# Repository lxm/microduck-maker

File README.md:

# MicroDuck Maker

**把 MicroDuck 从装配、标定到日常维护会用到的工具，放进一个持续维护的项目。**

[工具目录](tools/README.md) · [飞特舵机调试](tools/servo-debug/README.md) · [标定工具使用说明](tools/calibrator/README.md) · [装配对照](tools/servo-guide/README.md) · [下载发布包](https://github.com/lxm/microduck-maker/releases) · [反馈问题](https://github.com/lxm/microduck-maker/issues)

## 现在可以用什么

| 工具 | 用途 | 入口 |
|---|---|---|
| 飞特舵机调试 | USB 串口直连 HD-1910：搜索、微调、反馈曲线、校零与参数备份 | [tools/servo-debug](tools/servo-debug/) |
| 逐关节零位标定 | 单屏 3D 工作台、逐颗标定、回零 / HOME、保持与备份 | [tools/calibrator](tools/calibrator/) |
| 舵机编号与装配对照 | 飞特 HD-1910 版的 15 颗舵机位置、编号与装配检查 | [tools/servo-guide](tools/servo-guide/) · [在线查看](https://lxm.github.io/microduck-servo-guide/) |
| 零位标定支架 | 6 件 STL、装配参考与代打说明 | [tools/zero-fixture](tools/zero-fixture/) |
| 硅胶脚底翻模（正在尝试中） | 原尺寸版固定失败、需皮筋兜住；本次硅胶很防滑，后续 A–D 四版待实验 | [下载模具与使用方法](tools/silicone-sole-mold/) |
| 颈部舵机连接板 | D0.8.1 原配胶壳短线焊接版：KiCad、板级 3D、单板／六联制造文件与接线说明 | [tools/neck-interconnect](tools/neck-interconnect/) |

仓库包含标定与装配工具的源码、第三方资源、使用说明和离线验证程序，以及零位标定支架的 STL 打印文件（不含支架 STEP）、颈部连接板的可编辑 PCB 和板级 STEP。支架保留原设计，已知配合问题和来源说明见其目录。颈部板当前收录原配胶壳短线穿孔焊接版，替代端子试装版待验证后单独发布。

## Orange Pi Zero 3W 固件

基于 [kissqy/Microduck-kissqy（`d4d21c1`）](https://github.com/kissqy/Microduck-kissqy/tree/d4d21c1073d2c12ad2b5dfe3deb031030f7792ef)，保留原有机器人应用、模型和 ToF 源码，由 MicroDuck Maker 在 Armbian 26.8.1 上适配串口、HAT I²C 和音频。

摄像头版镜像请从 [Orange Pi 固件 Actions](https://github.com/lxm/microduck-maker/actions/workflows/orangepi-image.yml) 的成功构建下载。下方固定发布版 exp.1 早于摄像头适配。

[下载 exp.1 完整刷卡镜像（.img.xz）](https://github.com/lxm/microduck-maker/releases/download/orangepi-zero3w-exp.1/Microduck_OrangePiZero3W_Experimental.img.xz) · [SHA-256 校验文件](https://github.com/lxm/microduck-maker/releases/download/orangepi-zero3w-exp.1/SHA256SUMS) · [刷卡与首次启动说明](firmware/orangepi-zero3w/)

这是面向 Allwinner A733、1 GB、PCB V1.5 的实验镜像，已离线校验，尚未验证本发布镜像的实机启动。

## 先体验标定工具

电脑安装 Python **3.10+**，然后运行：

```sh
git clone https://github.com/lxm/microduck-maker.git
cd microduck-maker/tools/calibrator
python3 server.py --demo
```

打开 <http://127.0.0.1:8795/>。默认即为模拟模式，可以体验选关节、采样、保存和保持流程，不连接机器人。下载资源均包含在仓库中，不需要 npm 或在线 CDN。

需要另一台电脑访问时，在启动命令后加 `--bind 0.0.0.0`，然后用浏览器打开 `http://服务电脑的IPv4地址:8795/`。具体步骤与连接排查见 [局域网访问说明](tools/calibrator/docs/usage.md#从另一台电脑访问)。

实机标定还需要兼容的板端运行环境与 SSH。先读 [适用范围与连接方法](tools/calibrator/README.md#适用范围)，再按 [详细操作说明](tools/calibrator/docs/usage.md) 执行。机械零位和站立 HOME 是不同概念，3D 参考按钮只改变画面。

## 直接连接飞特舵机

电脑通过 USB 转 TTL 转接器连接 HD-1910 时，使用 [MicroDuck FD 调试工作台](tools/servo-debug/README.md)。macOS 可双击 `tools/servo-debug/启动调试工具.command`，或从仓库根目录执行：

```sh
zsh tools/servo-debug/启动调试工具.command
```

选择「演示设备」可先体验完整流程；实机使用前按工具说明核对供电、串口与波特率。它与通过 SSH 操作机器人主板的标定工具是两个独立入口。

## 项目结构

```text
microduck-maker/
├── tools/
│   ├── servo-debug/      # USB 串口舵机调试工作台与演示设备
│   ├── calibrator/       # 标定网页、板端代理、测试与说明
│   ├── servo-guide/      # 3D 舵机编号与装配对照
│   ├── zero-fixture/     # 零位标定支架 STL 与打印说明
│   ├── silicone-sole-mold/ # 硅胶脚套模具与浇注说明（正在尝试中）
│   └── neck-interconnect/ # 颈部连接板、板级模型与接线／打板说明
├── firmware/             # 按板型维护的固件源码与镜像构建说明
├── docs/                 # 项目维护与发布说明
├── scripts/              # 全仓库离线验证
├── .github/workflows/    # 自动校验
├── LICENSE              # 原创代码的 MIT 许可
└── THIRD_PARTY_NOTICES.md
```

每个工具在自己的目录内说明依赖、启动方式、兼容范围和来源，能够独立使用。后续新增工具继续放到 `tools/<工具名>/`，固件按板型放到 `firmware/<板型>/`。

## 开发与验证

安装 Python 3.10+ 和 Node.js。Node.js 仅用于 JavaScript 语法校验，不是标定工具的运行依赖。

```sh
python3 -m pip install -r tools/servo-debug/requirements.txt
python3 scripts/validate.py
```

验证包含飞特调试工具的模拟协议、校零与 HTTP 检查，以及标定工具及串口发现/依赖准备的离线测试、3D 引用文件哈希、网页静态资源，以及装配对照的网格、69 个装配变换和 15 个舵机编号、颈部板文件与制造包完整性。验证不连接机器人、不操作串口、不上传程序或改写实机。

当前工作台增加单屏布局与回 HOME 操作；离线测试通过不等同于跨机型实机验收。兼容条件及已知边界见各工具说明。贡献与发布方式见 [CONTRIBUTING.md](CONTRIBUTING.md) 和 [发布说明](docs/releasing.md)。

## 来源与许可

- 飞特舵机调试工作台继承原项目原创工具的 Apache-2.0 许可，来源和修改范围见 [工具说明](tools/servo-debug/README.md#目录与来源)。
- lxm 原创的标定界面、维护代理、脚本，以及装配对照的原创网页和提取代码采用 [MIT](LICENSE)。
- 标定工具引用的 Kissqy 参考代码保留其**个人非商业使用许可**；其 3D 模型与 Three.js 分别保留上游模型许可、MIT 许可。
- 装配工具的 CAD 衍生模型采用 **CC BY-NC-SA 4.0**，保留机械行者Robo、fanhao375 和 Pollen Robotics 的署名。
- 零位标定支架来自交流群分享，暂无原始发布链接，作者与模型许可尚未确认；其 STL 与模型截图不纳入软件 MIT 许可，详见该目录说明。
- 颈部板的原创 PCB、简化接线模型、脚本与说明适用 MIT；原配胶壳模型为示意，原厂舵机 CAD 未打包，见 [资料来源](tools/neck-interconnect/d0.8.1/docs/provenance.md)。
- 不同目录的许可范围见 [THIRD_PARTY_NOTICES.md](THIRD_PARTY_NOTICES.md)。MIT 不覆盖上述单独授权的资源，不能将整个下载包理解为统一 MIT 授权。

这是独立社区项目，与 Pollen Robotics、飞特及所引用社区项目无官方隶属或背书关系。现有 [microduck-servo-guide](https://github.com/lxm/microduck-servo-guide) 仓库和在线页面继续保留，新项目统一收录后续工具源码。

English: A growing collection of MicroDuck maker tools for assembly, servo zero calibration and maintenance. The calibration UI runs locally with an offline demo; hardware mode requires a compatible HD1910 robot environment. Third-party code and model assets retain their own licenses.

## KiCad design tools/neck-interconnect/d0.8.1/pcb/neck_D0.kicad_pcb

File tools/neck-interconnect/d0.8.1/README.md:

# D0.8.1 原配胶壳短线穿孔焊接版

整理日期：2026-11-02。设计快照：2026-11-01。

本版保留原配 AMP2.0 胶壳、压接触点和短线，裸线端穿过 J1–J4 的原通孔，在 PCB 外侧焊接。板厚 1.6mm，主体宽 20mm、包围尺寸 25.5×40mm，四个固定孔，外接凸台在正面左侧。PCB 直接贴舵机参考安装面，没有垫高结构；接头和线长以实物试装确定。

相比旧 D0.8，已修正 J1/J2 的 DATA/GND 铜网与编号，补齐六个端口及三个测试点的双面丝印，测试点加大为 Ø1.8mm 焊盘／Ø0.5mm 孔。旧错误包未收录。这里没有替代排母焊盘、大搭焊接线焊盘或 7343 电容封装。

## 下载与打开

- [KiCad 工程](pcb/neck_D0.kicad_pro)、[PCB](pcb/neck_D0.kicad_pcb)、[原理图](pcb/neck_D0.kicad_sch)。整目录下载后，用 KiCad 10 打开工程；本地符号库、封装库与模型按相对路径组织。
- [不含舵机的 PCB 查看副本](pcb/neck_D0_8_1_no_servos.kicad_pcb)、[完全裸板查看副本](pcb/neck_D0_8_1_bare_pcb_view.kicad_pcb)。主工程同样只收录板级模型。PCB 编辑器中用“视图 → 3D 查看器”查看，切换正反面。
- [板级 STEP](mechanical/KiCad_Neck_D0_8_1_PCB_only.step)，可用 FreeCAD 等查看。包含 PCB、铜与简化连接器／线端模型，不含原厂舵机 CAD。
- [单板 Gerber ZIP](fabrication/D0_8_1_1oz_single/MicroDuck_Neck_D0.8.1_1oz_single_25.5x40_PINOUT_CHECK.zip)、[六联 Gerber ZIP](fabrication/D0_8_1_1oz_6up/MicroDuck_Neck_D0.8.1_1oz_6up_94.5x96_PINOUT_CHECK.zip)。在 GitHub 文件页点击下载原始文件，再将 ZIP 上传打板平台。
- [物料表](bom.csv)、[接线装配](docs/assembly.md)、[针序表](docs/pinout-and-testpoints.md)、[打板参数](docs/fabrication.md)。

## 正反面

下图为裸板，不显示连接器。F 面朝外，B 面朝舵机。正面凸台在左，翻到背面后自然显示在右侧。

## 供电与验收状态

六个端口并联：1=DATA，2=VBUS_SERVO，3=GND。**+ 为电池母线，2S 最高 8.4V；本板没有降压电路。** 头部若使用 Zero 3W 等主板，应由对应供电电路降压后接入，不能把该 + 直接当作 5V。

本版内部 ERC、DRC、针序、丝印、测试点、六联一致性及 Gerber 导出检查通过。整理后再次运行主工程 ERC、DRC 和原理图一致性检查；[当前打包 DRC](validation/packaged-drc.json)、[ERC](validation/packaged-erc.json)、[文件清单](manifest.json)及[原检查记录](validation/original/)一并保留。

J1/J2 的修正来自先前实物错误反馈；**J5/J6 外接线束另一端极性仍待实物核对**。短线穿孔、螺钉规格和有效深度、完整运动范围、接线抗拉及实际负载温升也尚未完成样板验收。检查通过表示文件内部一致，不表示整机配合已经验证。使用前按装配说明逐项核对。

PCB、原创脚本和说明适用仓库 MIT 许可。连接器模型按尺寸简化，原配胶壳／线端仅作装配示意，不是供应商精确 CAD 或替代接头认证。来源与整理改动见 [provenance.md](docs/provenance.md)。

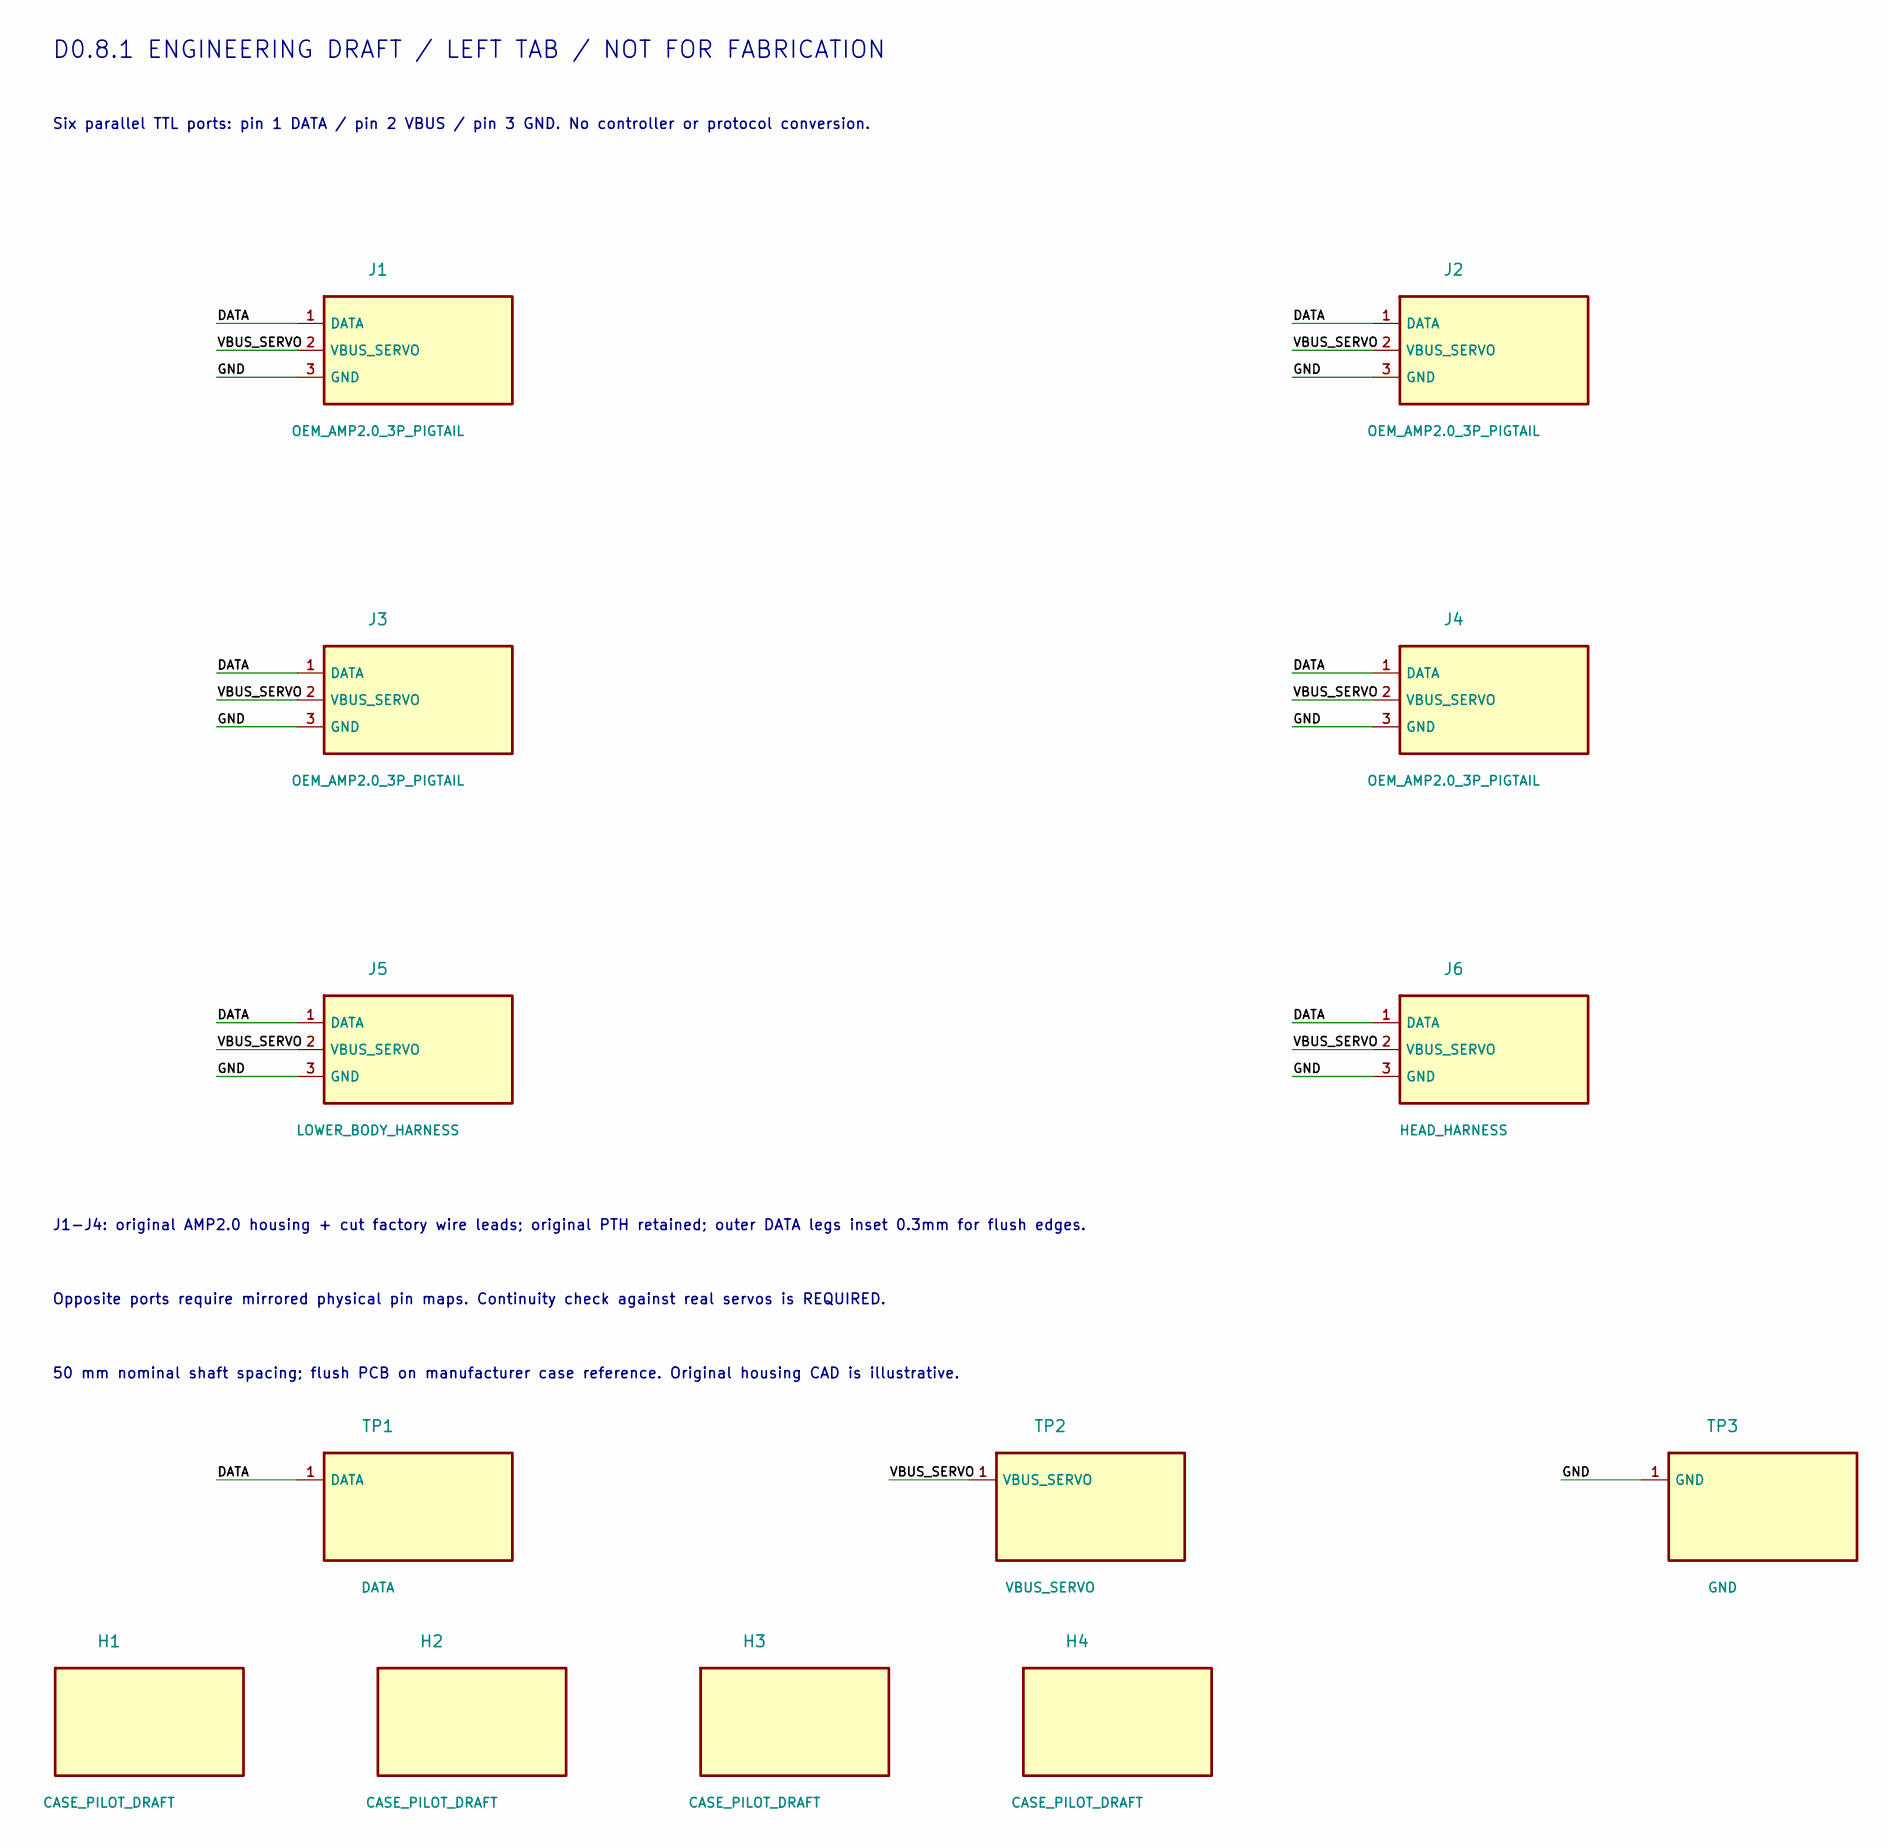
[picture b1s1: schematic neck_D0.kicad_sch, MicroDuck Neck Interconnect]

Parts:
H1: CASE_PILOT_DRAFT; CaseMount_Lower_AssemblyReference
H2, H4: CASE_PILOT_DRAFT; CaseMount_D2
H3: CASE_PILOT_DRAFT; CaseMount_Upper_AssemblyReference
J1, J3: OEM_AMP2.0_3P_PIGTAIL; OEM_WirePTH_P2mm_Pin1Left; MPN NOT_IDENTIFIED_OEM_SUPPLIED
J2, J4: OEM_AMP2.0_3P_PIGTAIL; OEM_WirePTH_P2mm_Pin1Right; MPN NOT_IDENTIFIED_OEM_SUPPLIED
J5: LOWER_BODY_HARNESS; CJT_A2007WV_3P; MPN A2007WV-3P
J6: HEAD_HARNESS; CJT_A2007WV_3P; MPN A2007WV-3P
TP1: DATA; TP_PTH_1p8
TP2: VBUS_SERVO; TP_PTH_1p8
TP3: GND; TP_PTH_1p8

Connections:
/DATA: J1.1 (DATA), J2.1 (DATA), J3.1 (DATA), J4.1 (DATA), J5.1 (DATA), J6.1 (DATA), TP1.1
/GND: J1.3 (GND), J2.3 (GND), J3.3 (GND), J4.3 (GND), J5.3 (GND), J6.3 (GND), TP3.1
/VBUS_SERVO: J1.2 (VBUS_SERVO), J2.2 (VBUS_SERVO), J3.2 (VBUS_SERVO), J4.2 (VBUS_SERVO), J5.2 (VBUS_SERVO), J6.2 (VBUS_SERVO), TP2.1

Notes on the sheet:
D0.8.1 ENGINEERING DRAFT / LEFT TAB / NOT FOR FABRICATION
Six parallel TTL ports: pin 1 DATA / pin 2 VBUS / pin 3 GND. No controller or protocol conversion.
J1-J4: original AMP2.0 housing + cut factory wire leads; original PTH retained; outer DATA legs inset 0.3mm for flush edges.
Opposite ports require mirrored physical pin maps. Continuity check against real servos is REQUIRED.
50 mm nominal shaft spacing; flush PCB on manufacturer case reference. Original housing CAD is illustrative.

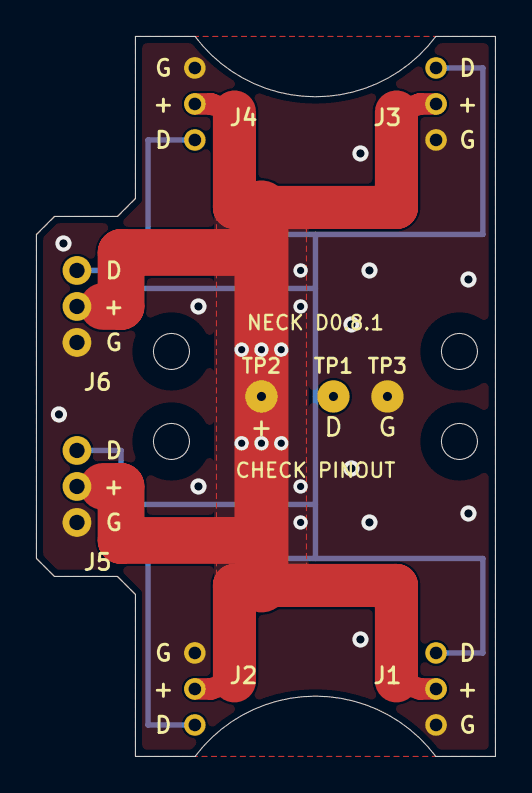
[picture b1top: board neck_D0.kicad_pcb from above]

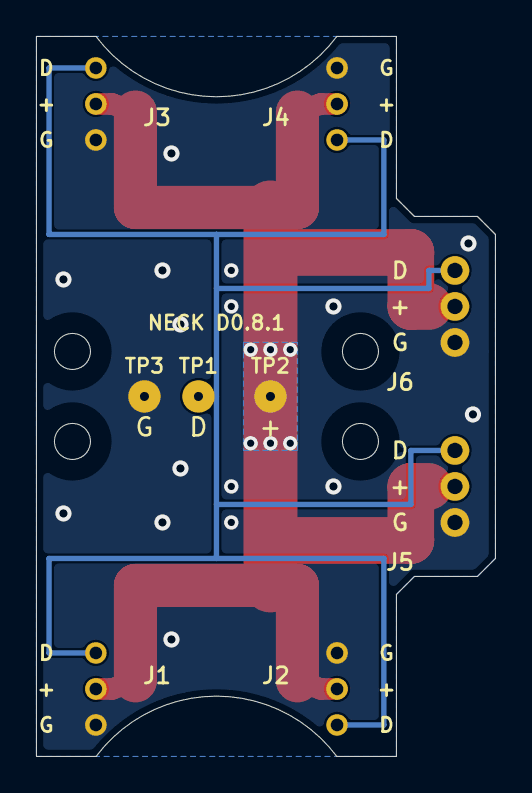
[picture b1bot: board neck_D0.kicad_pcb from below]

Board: 2 copper layers, 25.5 x 40.0 mm, 13 parts (6 on the bottom side), 3 nets.

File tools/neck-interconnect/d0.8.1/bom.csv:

Reference,Qty,Value,Footprint,MPN,Manufacturer,Chosen_Distributor,Datasheet,Validated,DNP,Notes
"J1,J3",2,OEM_AMP2.0_3P_PIGTAIL,OEM_WirePTH_P2mm_Pin1Left,NOT_IDENTIFIED_OEM_SUPPLIED,FEETECH supplied harness,,,,,Reuse one original servo-supplied AMP2.0 plug with 3 factory wires per port. Trim/strip ends to original 0.70mm PTH; solder only outside. Original wire OD and plug seating need dry fit.
"J2,J4",2,OEM_AMP2.0_3P_PIGTAIL,OEM_WirePTH_P2mm_Pin1Right,NOT_IDENTIFIED_OEM_SUPPLIED,FEETECH supplied harness,,,,,Reuse one original servo-supplied AMP2.0 plug with 3 factory wires per port. Trim/strip ends to original 0.70mm PTH; solder only outside. Original wire OD and plug seating need dry fit.
J5,1,LOWER_BODY_HARNESS,CJT_A2007WV_3P,A2007WV-3P,CJT,,https://www.cjt.com/upload/A2007.pdf,,,External harness socket; mating compatibility and wire orientation require sample check.
J6,1,HEAD_HARNESS,CJT_A2007WV_3P,A2007WV-3P,CJT,,https://www.cjt.com/upload/A2007.pdf,,,External harness socket; mating compatibility and wire orientation require sample check.

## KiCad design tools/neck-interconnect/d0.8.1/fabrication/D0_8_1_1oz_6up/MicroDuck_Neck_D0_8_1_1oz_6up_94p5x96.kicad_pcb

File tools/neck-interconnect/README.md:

# 颈部舵机连接板

将两只颈部舵机的 DATA、电池电源与地汇接到一块 PCB，通过左侧两个插座连接下半身和头部，减少颈部独立线束。PCB 主体与舵机参考外壳齐边，直接贴壳安装，不设垫柱。

当前收录 **[D0.8.1 原配胶壳短线穿孔焊接版](d0.8.1/README.md)**。它使用舵机原配 AMP2.0 胶壳、原压接触点和剪短的原配线，线端穿 PCB 通孔，在外侧焊接。J5/J6 使用 A2007WV-3P。它是带检查记录的原型资料，不是已完成整机实物验收的成品设计。

## 焊线方案装配效果参考

以下为 **D0.11 大焊盘＋电容版**的正反面 3D 图，展示原配胶壳、短线和外接插座的装配方式。正反面采用相同的正投影视角、背景和渲染风格；背面凸台因翻面显示在右侧。它与当前收录的 **D0.8.1 穿孔版不同**，图中的大搭焊焊盘和 C1 电容不包含在当前下载的制造文件中。

| 正面：短线与电容 | 背面：原配胶壳与外接插座 |
| --- | --- |
|  |  |

[查看正面原图](docs/d0.11-reference/cap-front.png) · [查看背面原图](docs/d0.11-reference/cap-back.png) · [图片版本与来源](docs/d0.11-reference/README.md)

## 文件与说明

| 内容 | 入口 |
| --- | --- |
| 版本说明、PCB 与 3D | [D0.8.1](d0.8.1/README.md) |
| 接线与焊接步骤 | [装配说明](d0.8.1/docs/assembly.md) |
| D／+／G 针序、测试点 | [针序表](d0.8.1/docs/pinout-and-testpoints.md) |
| 单板、六联文件与下单参数 | [制造文件](d0.8.1/docs/fabrication.md) |
| 来源、整理范围和校验 | [资料来源](d0.8.1/docs/provenance.md) |

后续通孔／贴片排母兼容试装版暂未收录。待具体端子的针型、插入深度、贴壳间隙及负载表现验证后，再单独发布；当前制造文件不包含其贴片焊盘。旧 D0.8 的 J1/J2 曾出现 D/G 反接，本目录只提供修正后的 D0.8.1，不能用旧包替换。

离线检查：

```sh
python3 tools/neck-interconnect/scripts/validate.py
```

该检查不需要 KiCad、不连接机器人，核对归档文件哈希、模型路径、制造 ZIP 与针序检查记录。编辑电路后还需在 KiCad 中运行 ERC、DRC 和原理图一致性检查，重新生成制造文件。

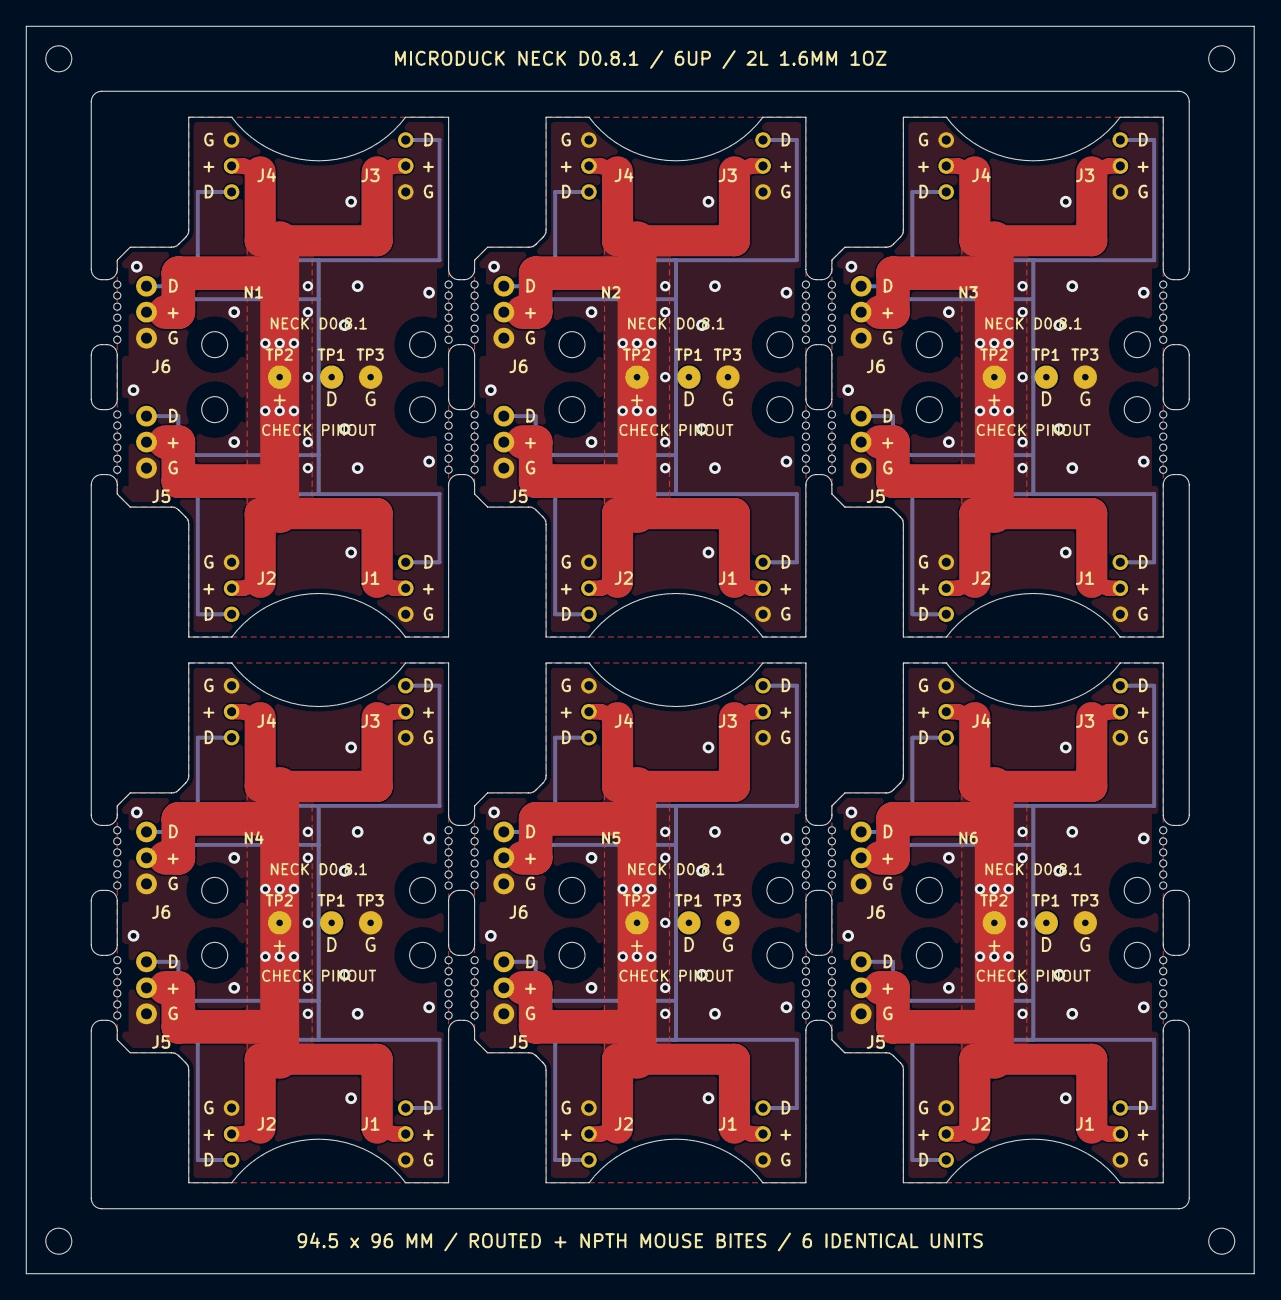
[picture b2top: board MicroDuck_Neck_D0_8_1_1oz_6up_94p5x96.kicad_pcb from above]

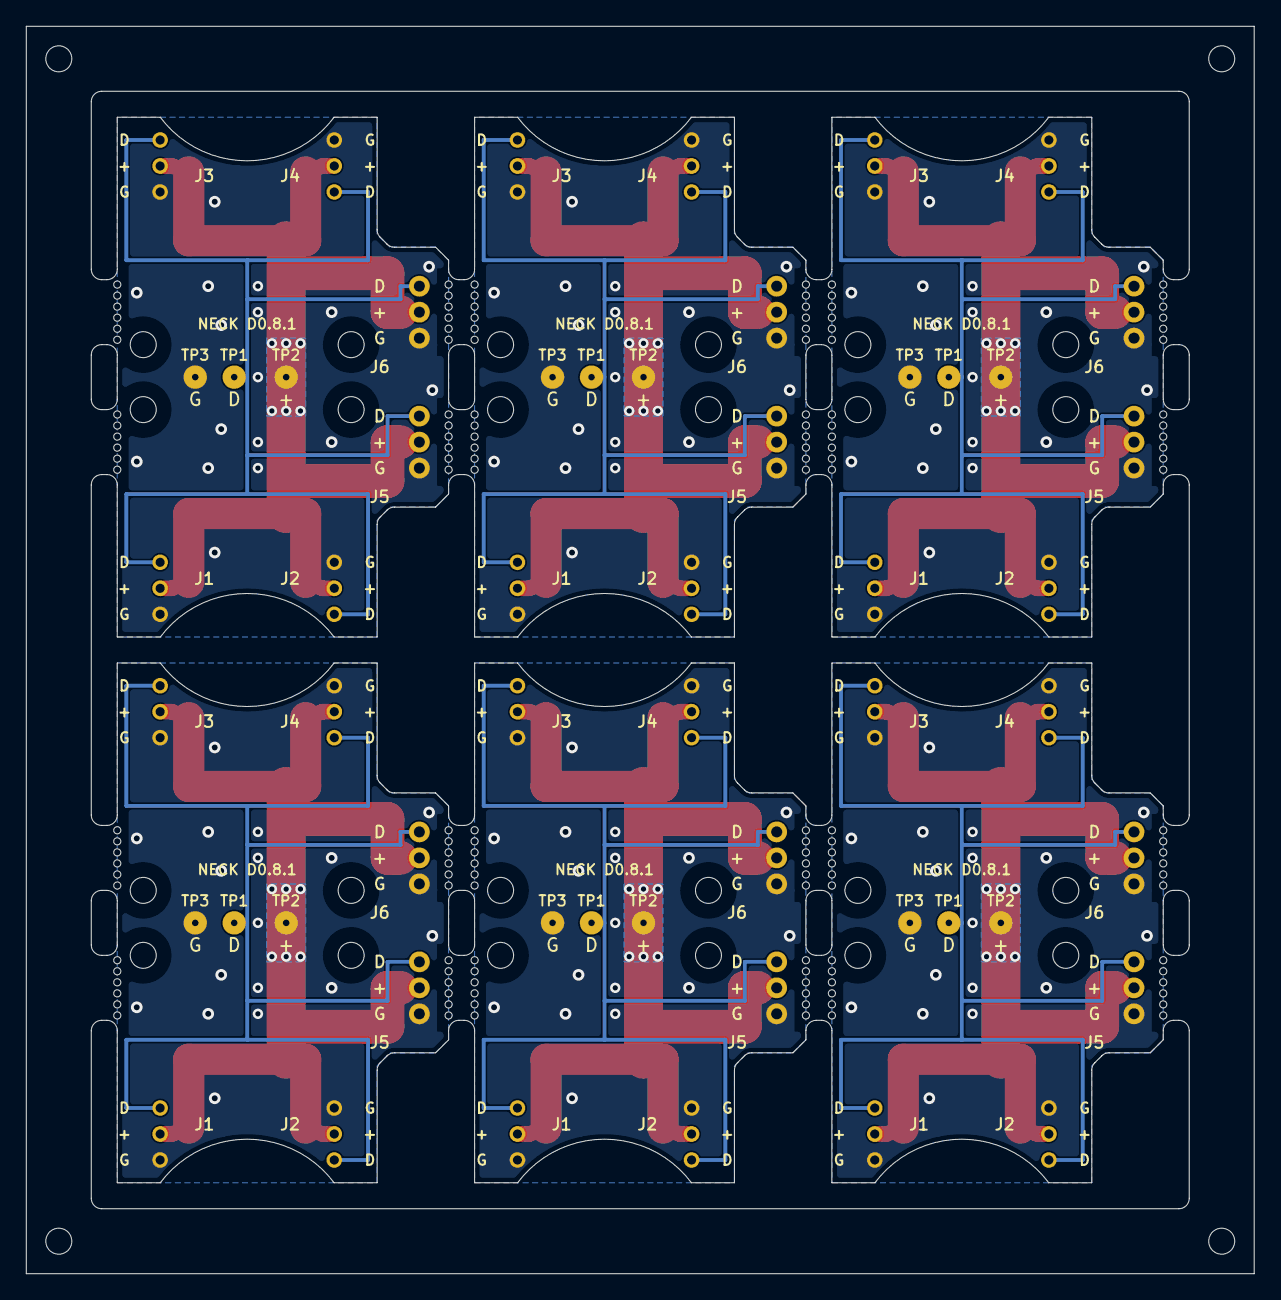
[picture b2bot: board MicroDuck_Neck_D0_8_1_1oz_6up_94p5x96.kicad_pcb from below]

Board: 2 copper layers, 94.5 x 96.0 mm, 80 parts (36 on the bottom side), 18 nets.

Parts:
MB1: NPTH_0.55
TOOL1: NPTH_2
U1_H1, U1_H2, U1_H3, U1_H4, U2_H1, U2_H2, U2_H3, U2_H4, U3_H1, U3_H2, U3_H3, U3_H4, U4_H1, U4_H2, U4_H3, U4_H4, U5_H1, U5_H2, U5_H3, U5_H4, U6_H1, U6_H2, U6_H3, U6_H4: CASE_PILOT_DRAFT
U1_J1, U1_J2, U1_J3, U1_J4, U2_J1, U2_J2, U2_J3, U2_J4, U3_J1, U3_J2, U3_J3, U3_J4, U4_J1, U4_J2, U4_J3, U4_J4, U5_J1, U5_J2, U5_J3, U5_J4, U6_J1, U6_J2, U6_J3, U6_J4: OEM_AMP2.0_3P_PIGTAIL
U1_J5, U2_J5, U3_J5, U4_J5, U5_J5, U6_J5: LOWER_BODY_HARNESS
U1_J6, U2_J6, U3_J6, U4_J6, U5_J6, U6_J6: HEAD_HARNESS
U1_TP1, U2_TP1, U3_TP1, U4_TP1, U5_TP1, U6_TP1: DATA
U1_TP2, U2_TP2, U3_TP2, U4_TP2, U5_TP2, U6_TP2: VBUS_SERVO
U1_TP3, U2_TP3, U3_TP3, U4_TP3, U5_TP3, U6_TP3: GND

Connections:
/U1/DATA: U1_J1.1, U1_J2.1, U1_J3.1, U1_J4.1, U1_J5.1, U1_J6.1, U1_TP1.1
/U1/GND: U1_J1.3, U1_J2.3, U1_J3.3, U1_J4.3, U1_J5.3, U1_J6.3, U1_TP3.1
/U1/VBUS_SERVO: U1_J1.2, U1_J2.2, U1_J3.2, U1_J4.2, U1_J5.2, U1_J6.2, U1_TP2.1
/U2/DATA: U2_J1.1, U2_J2.1, U2_J3.1, U2_J4.1, U2_J5.1, U2_J6.1, U2_TP1.1
/U2/GND: U2_J1.3, U2_J2.3, U2_J3.3, U2_J4.3, U2_J5.3, U2_J6.3, U2_TP3.1
/U2/VBUS_SERVO: U2_J1.2, U2_J2.2, U2_J3.2, U2_J4.2, U2_J5.2, U2_J6.2, U2_TP2.1
/U3/DATA: U3_J1.1, U3_J2.1, U3_J3.1, U3_J4.1, U3_J5.1, U3_J6.1, U3_TP1.1
/U3/GND: U3_J1.3, U3_J2.3, U3_J3.3, U3_J4.3, U3_J5.3, U3_J6.3, U3_TP3.1
/U3/VBUS_SERVO: U3_J1.2, U3_J2.2, U3_J3.2, U3_J4.2, U3_J5.2, U3_J6.2, U3_TP2.1
/U4/DATA: U4_J1.1, U4_J2.1, U4_J3.1, U4_J4.1, U4_J5.1, U4_J6.1, U4_TP1.1
/U4/GND: U4_J1.3, U4_J2.3, U4_J3.3, U4_J4.3, U4_J5.3, U4_J6.3, U4_TP3.1
/U4/VBUS_SERVO: U4_J1.2, U4_J2.2, U4_J3.2, U4_J4.2, U4_J5.2, U4_J6.2, U4_TP2.1
/U5/DATA: U5_J1.1, U5_J2.1, U5_J3.1, U5_J4.1, U5_J5.1, U5_J6.1, U5_TP1.1
/U5/GND: U5_J1.3, U5_J2.3, U5_J3.3, U5_J4.3, U5_J5.3, U5_J6.3, U5_TP3.1
/U5/VBUS_SERVO: U5_J1.2, U5_J2.2, U5_J3.2, U5_J4.2, U5_J5.2, U5_J6.2, U5_TP2.1
/U6/DATA: U6_J1.1, U6_J2.1, U6_J3.1, U6_J4.1, U6_J5.1, U6_J6.1, U6_TP1.1
/U6/GND: U6_J1.3, U6_J2.3, U6_J3.3, U6_J4.3, U6_J5.3, U6_J6.3, U6_TP3.1
/U6/VBUS_SERVO: U6_J1.2, U6_J2.2, U6_J3.2, U6_J4.2, U6_J5.2, U6_J6.2, U6_TP2.1
